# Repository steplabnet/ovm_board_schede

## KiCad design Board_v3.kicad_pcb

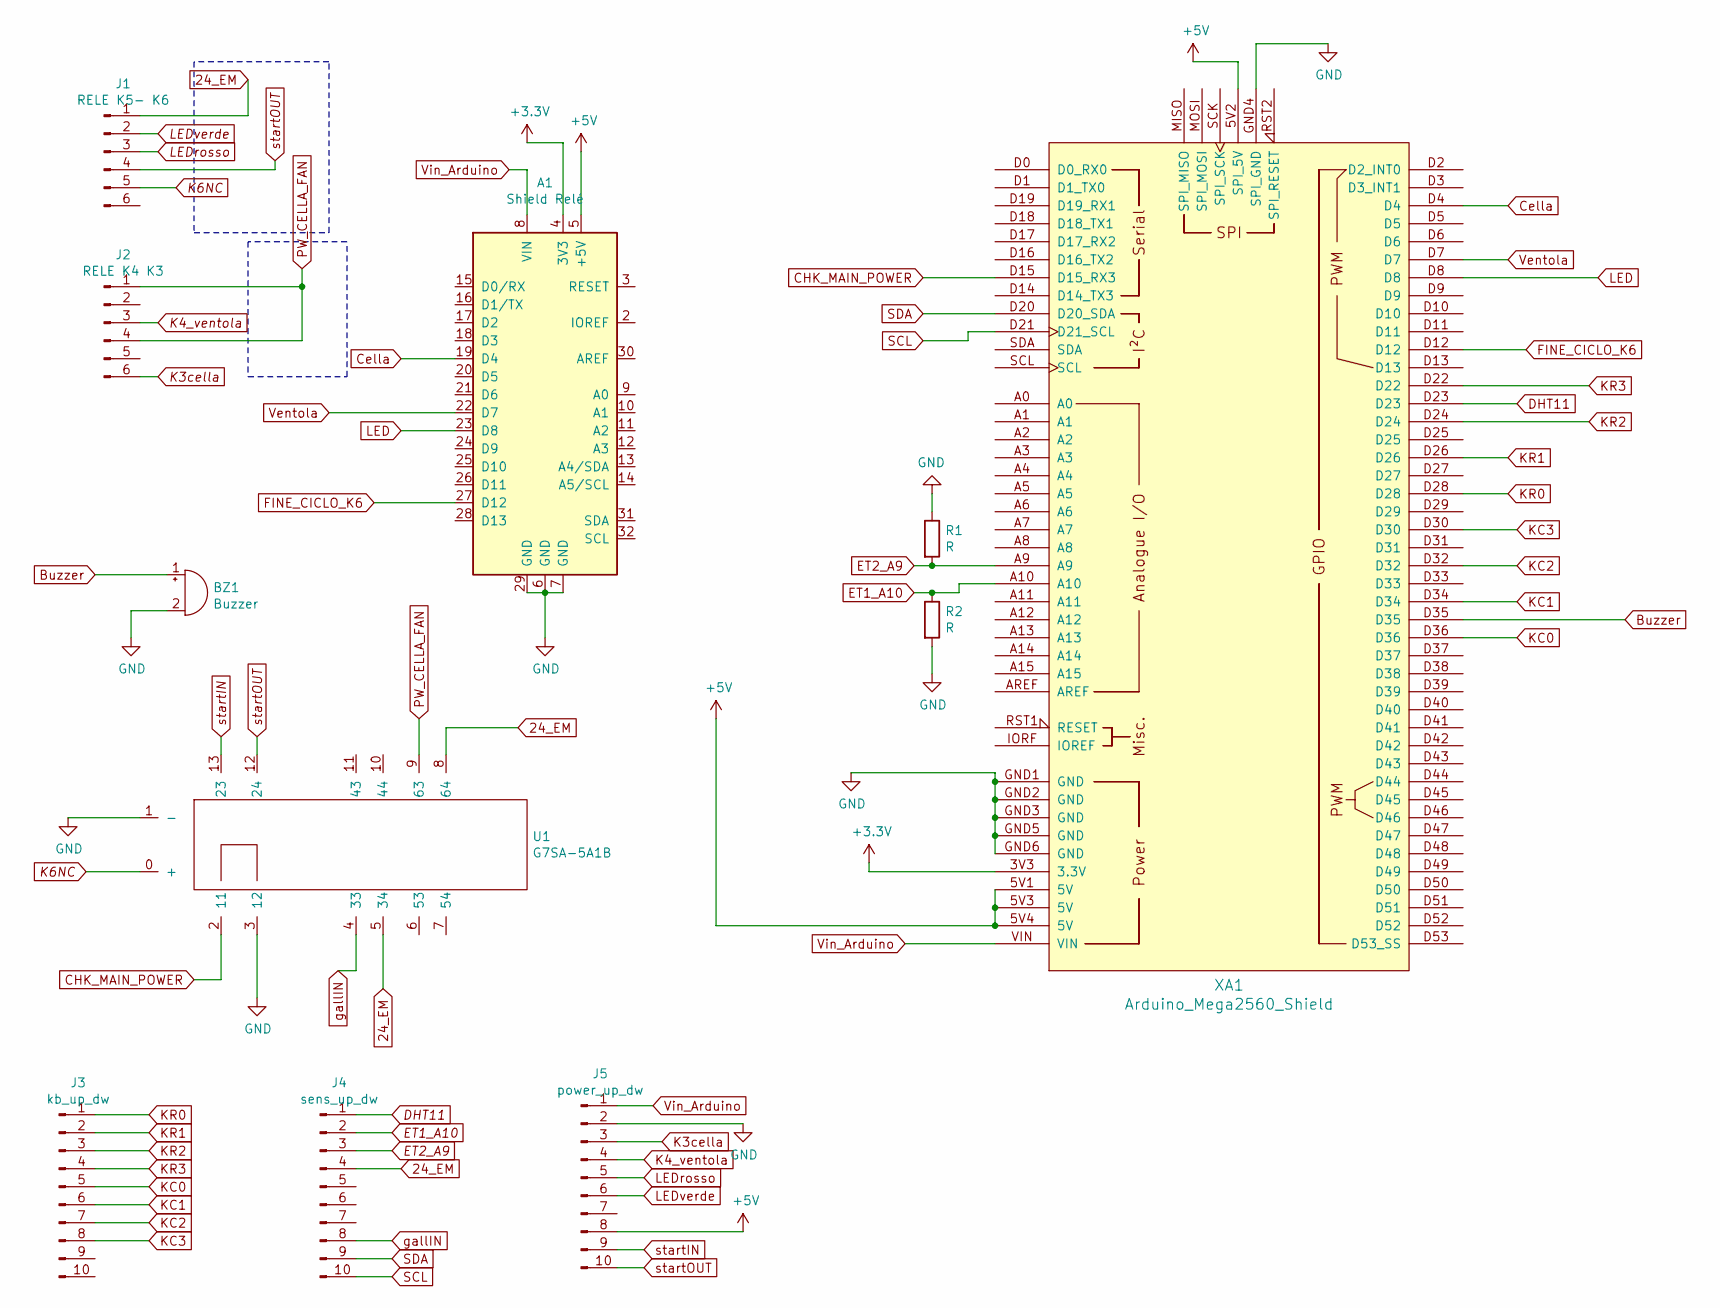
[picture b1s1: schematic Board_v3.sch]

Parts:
A1: Shield Relé; Arduino_UNO_R3
BZ1: Buzzer; PhoenixContact_MSTBVA_2,5_2-G_1x02_P5.00mm_Vertical
J1: RELE K5- K6; PhoenixContact_MCV_1,5_6-G-3.5_1x06_P3.50mm_Vertical
J2: RELE K4 K3; PhoenixContact_MCV_1,5_6-G-3.5_1x06_P3.50mm_Vertical
J3: kb_up_dw; PinHeader_1x10_P2.54mm_Vertical
J4: sens_up_dw; PinHeader_1x10_P2.54mm_Vertical
J5: power_up_dw; PinHeader_1x10_P2.54mm_Vertical
R1, R2: R; R_Axial_DIN0207_L6.3mm_D2.5mm_P15.24mm_Horizontal
U1: G7SA-5A1B
XA1: Arduino_Mega2560_Shield

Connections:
24_EM: J1.1, J4.4, U1.5 (34), U1.8 (64)
+3V3: A1.4 (3V3), XA1.3V3 (3.3V)
+5V: A1.5 (+5V), J5.8, XA1.5V1 (5V), XA1.5V2 (SPI_5V), XA1.5V3 (5V), XA1.5V4 (5V)
Buzzer: BZ1.1 (-), XA1.D35
CHK_MAIN_POWER: U1.2 (11), XA1.D15 (D15_RX3)
Cella: A1.19 (D4), XA1.D4
DHT11: J4.1, XA1.D23
ET1_A10: J4.2, R2.1, XA1.A10
ET2_A9: J4.3, R1.2, XA1.A9
FINE_CICLO_K6: A1.27 (D12), XA1.D12
GND: A1.6 (GND), A1.7 (GND), A1.29 (GND), BZ1.2 (+), J5.2, R1.1, R2.2, U1.1 (-), U1.3 (12), XA1.GND1 (GND), XA1.GND2 (GND), XA1.GND3 (GND), XA1.GND4 (SPI_GND), XA1.GND5 (GND), XA1.GND6 (GND)
K3cella: J2.6, J5.3
K4_ventola: J2.3, J5.4
K6NC: J1.5, U1.0 (+)
KC0: J3.5, XA1.D36
KC1: J3.6, XA1.D34
KC2: J3.7, XA1.D32
KC3: J3.8, XA1.D30
KR0: J3.1, XA1.D28
KR1: J3.2, XA1.D26
KR2: J3.3, XA1.D24
KR3: J3.4, XA1.D22
LED: A1.23 (D8), XA1.D8
LEDrosso: J1.3, J5.5
LEDverde: J1.2, J5.6
PW_CELLA_FAN: J2.1, J2.4, U1.9 (63)
SCL: J4.10, XA1.D21 (D21_SCL)
SDA: J4.9, XA1.D20 (D20_SDA)
Ventola: A1.22 (D7), XA1.D7
Vin_Arduino: A1.8 (VIN), J5.1, XA1.VIN
gallIN: J4.8, U1.4 (33)
startIN: J5.9, U1.13 (23)
startOUT: J1.4, J5.10, U1.12 (24)

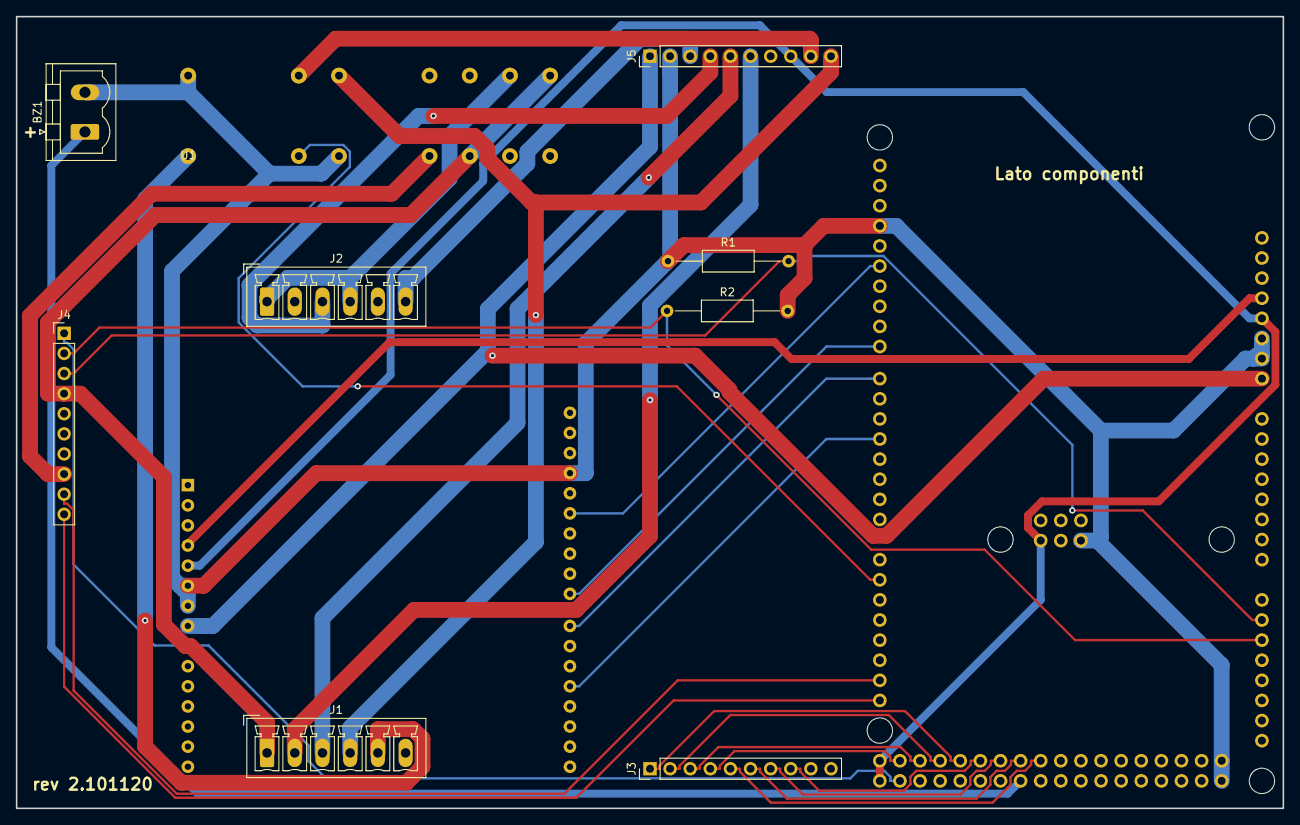
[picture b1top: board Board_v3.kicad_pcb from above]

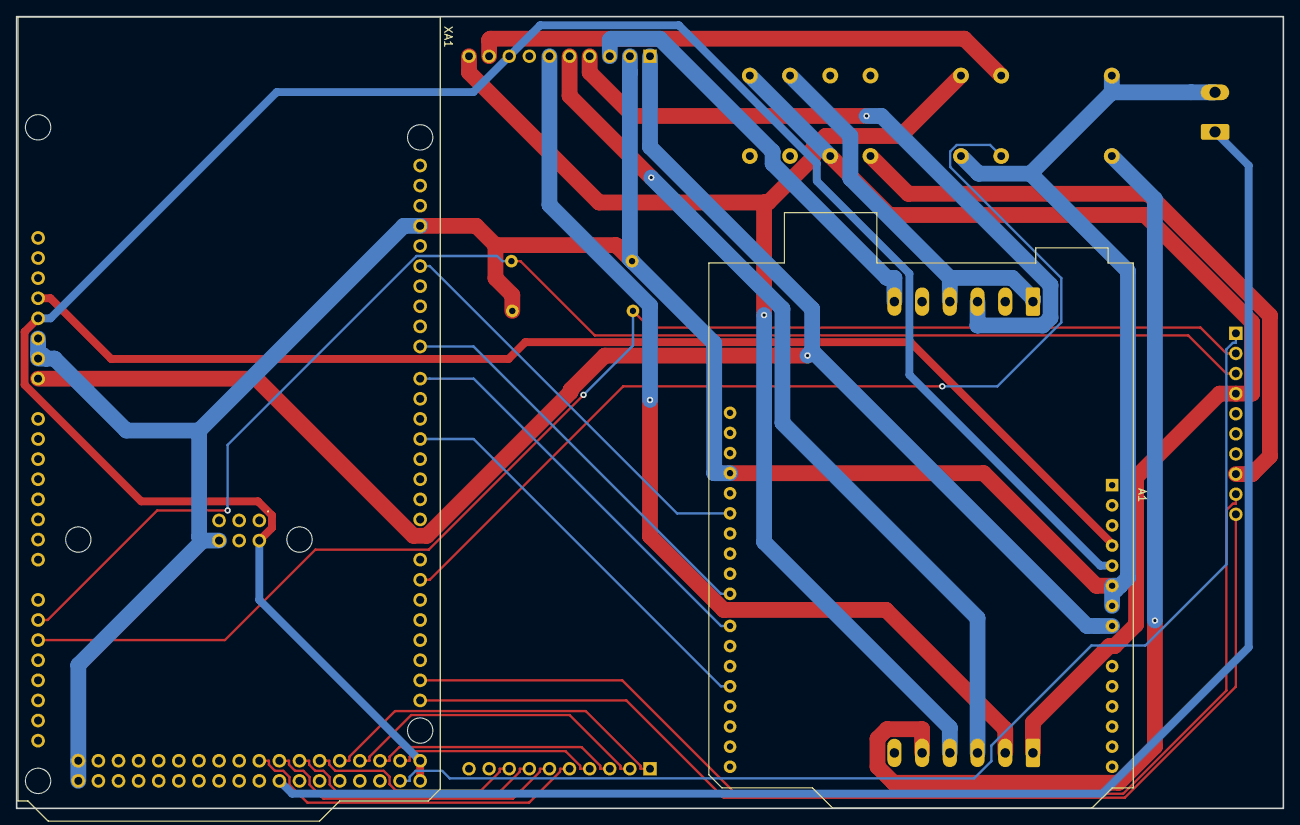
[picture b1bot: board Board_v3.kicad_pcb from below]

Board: 2 copper layers, 160.0 x 100.0 mm, 11 parts (2 on the bottom side), 33 nets.
